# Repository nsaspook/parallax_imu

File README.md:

# vcan

pic32mkmc Viision can motor tester
# parallax_imu

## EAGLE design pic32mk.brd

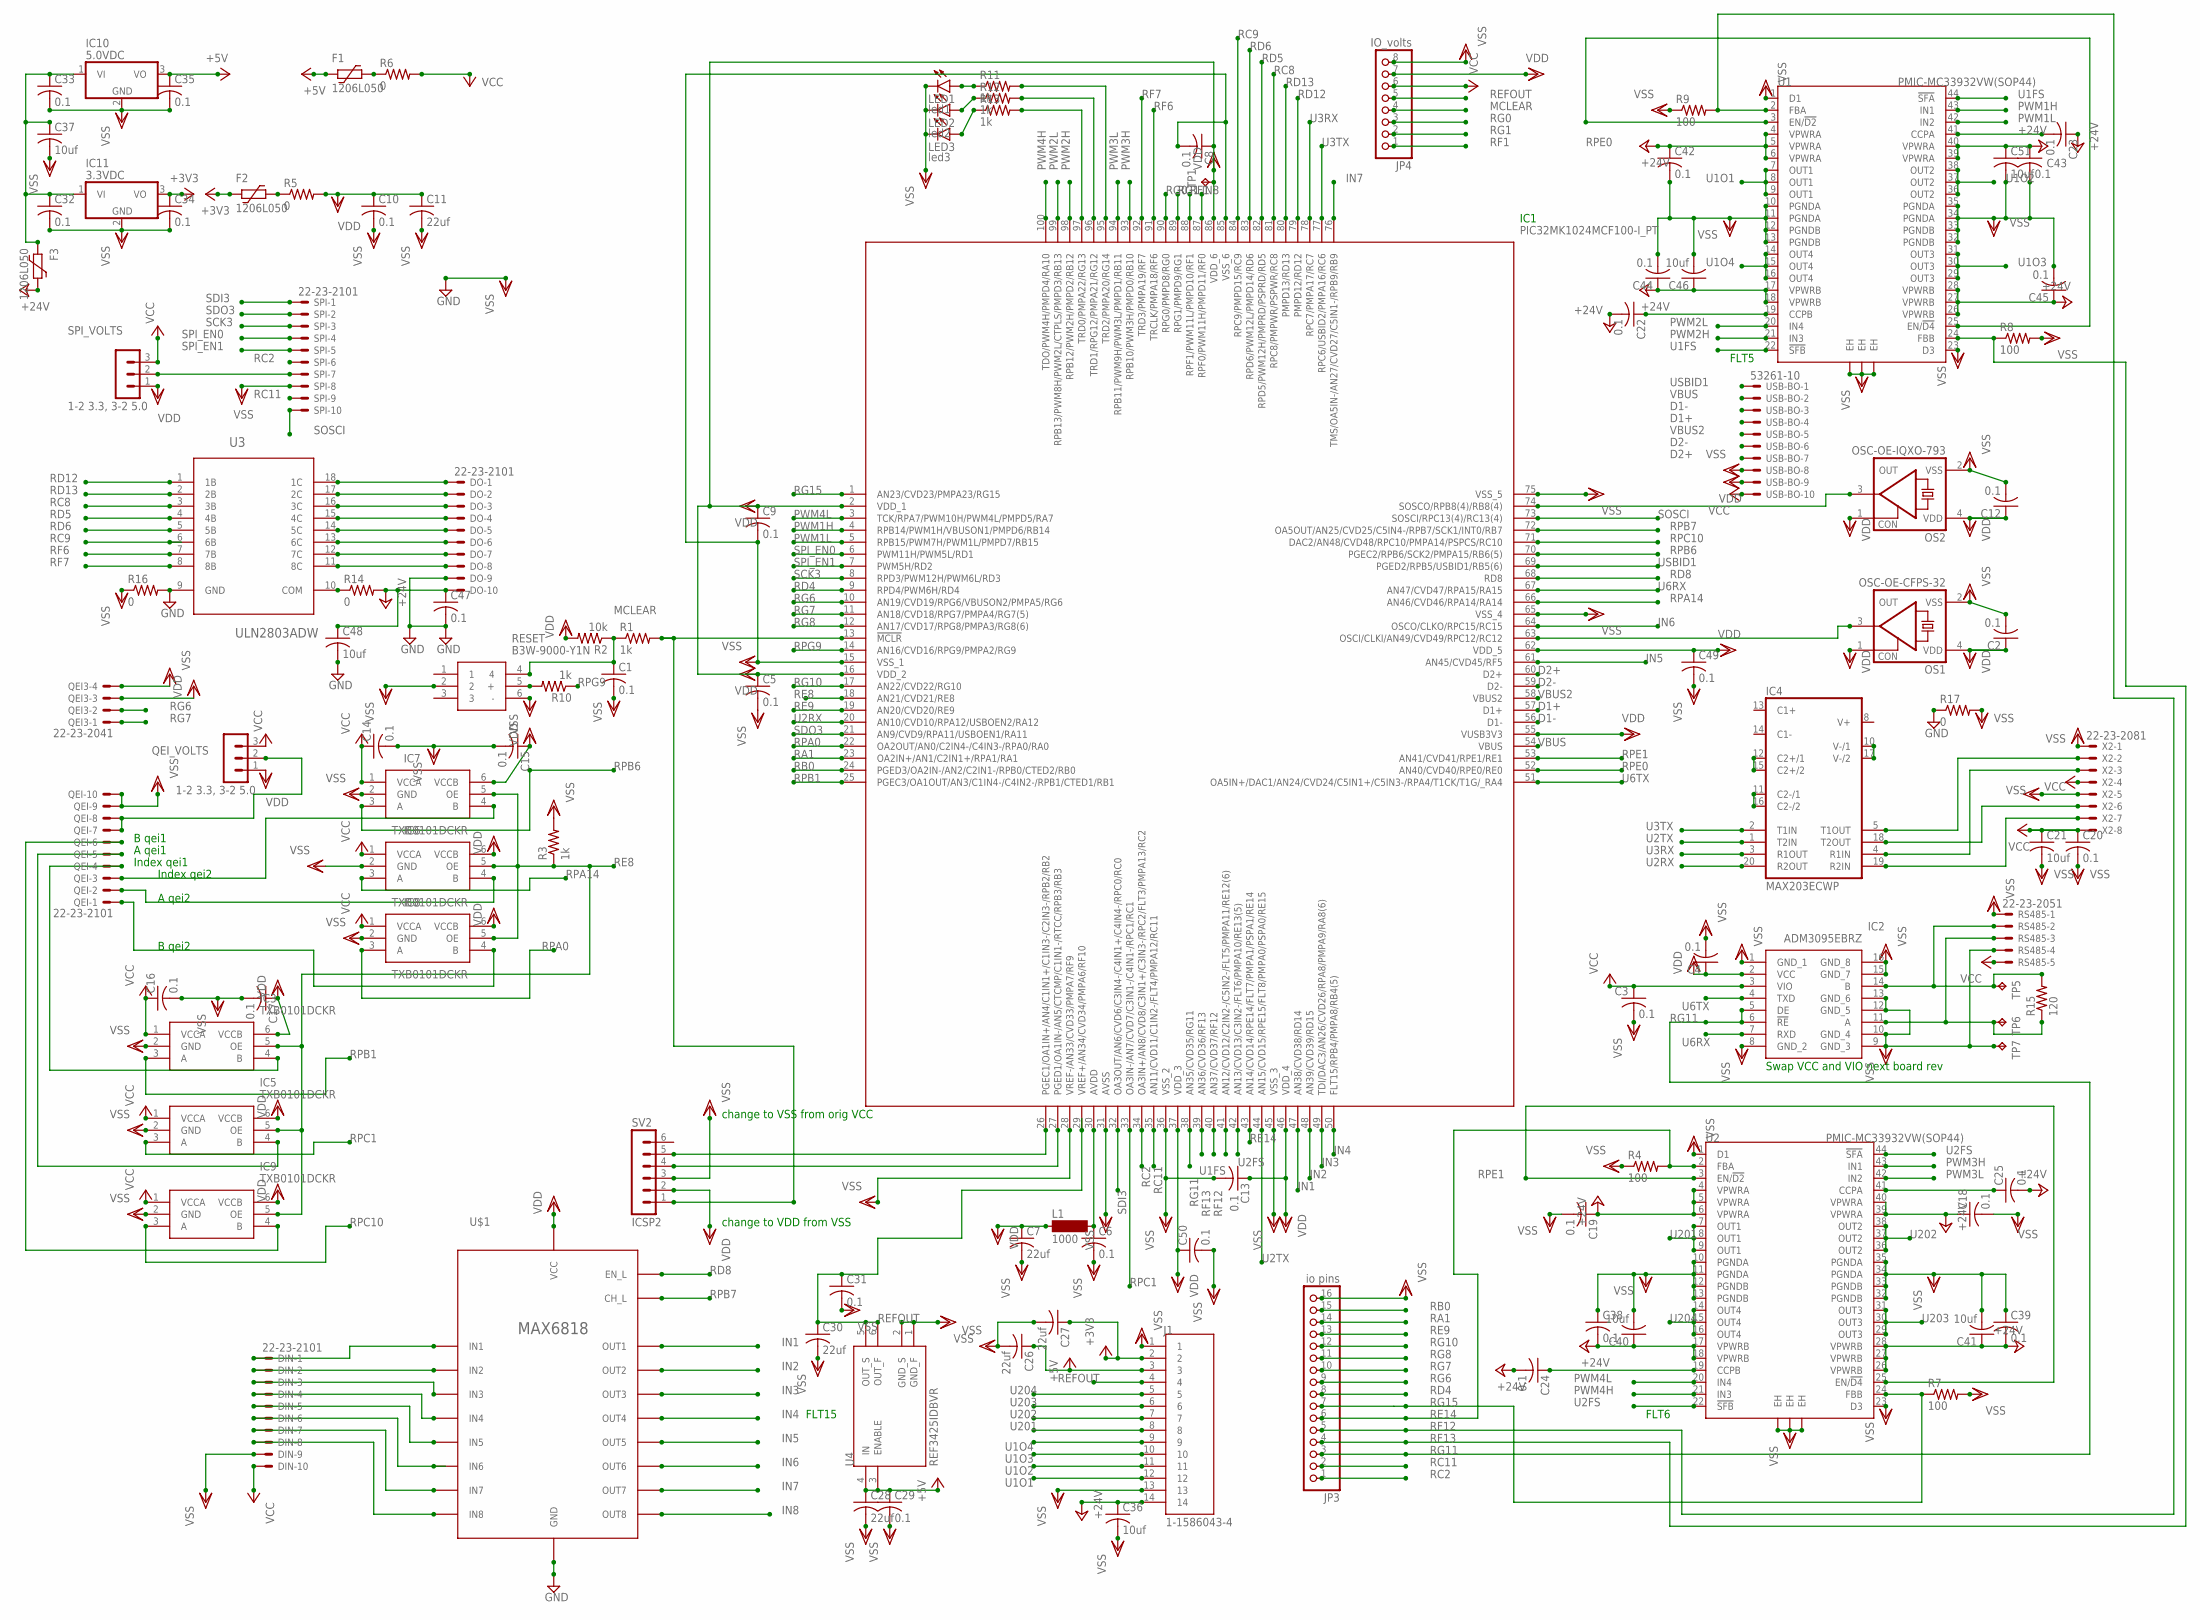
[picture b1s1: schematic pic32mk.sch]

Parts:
C1, C2, C3, C4, C5, C6, C8, C9, C10, C12, C13, C14, C15, C16, C17, C18, C19, C20, C22, C23, C24, C25, C29, C31, C32, C33, C34, C35, C38, C39, C42, C43, C44, C45, C47, C49, C50: 0.1; C0805
C7, C11, C26, C27, C28, C30: 22uf; C0805
C21, C36, C37, C40, C41, C46, C48, C51: 10uf; C1206
DIN: 22-23-2101
DO: 22-23-2101
F1, F2, F3: 1206L050; 1206L
IC1: PIC32MK1024MCF100-I_PT; QFP40P1400X1400X120-100N
IC2: ADM3095EBRZ; SOIC127P600X175-16N
IC3, IC5, IC6, IC7, IC8, IC9: TXB0101DCKR; SOT65P210X110-6N
IC4: MAX203ECWP; SO20L
IC10: 5.0VDC; TO220H
IC11: 3.3VDC; TO220H
J1: 1-1586043-4; TE_1-1586043-4
JP3: io pins; 1X16
JP4: IO_volts; 1X08
L1: 1000; SM-1206
LED1: led1; CHIPLED_1206
LED2: led2; CHIPLED_1206
LED3: led3; CHIPLED_1206
OS1: OSC-OE-CFPS-32; 7.2X5.2-4-PAD
OS2: OSC-OE-IQXO-793; 2.5X2-4-PAD
QEI: 22-23-2101
QEI3: 22-23-2041
QEI_VOLTS: 1-2 3.3, 3-2 5.0; MA03-1
R1, R3, R10, R11, R12, R13: 1k; M0805
R2: 10k; M0805
R4, R7, R8, R9: 100; R0805
R5, R6, R14, R16, R17: 0; M0805
R15: 120; R0805
RESET: B3W-9000-Y1N; B3W-9_1-LED
RS485: 22-23-2051
SPI: 22-23-2101
SPI_VOLTS: 1-2 3.3, 3-2 5.0; MA03-1
SV2: ICSP2; MA06-1
TP1, TP5, TP6, TP7: TPB1,27; B1,27
U1, U2: PMIC-MC33932VW(SOP44); SOP44-0.65-15.8X10.9MM
U3: ULN2803ADW; SOIC127P1030X265-18N
U4: REF3425IDBVR; SOT95P280X145-6N
U$1: MAX6818; SSOP20
USB-BO: 53261-10
X2: 22-23-2081

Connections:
+3V3: C27.1, C34.1, F2.2, IC11.3 (VO), J1.2
+5V: C26.1, C28.1, C29.1, C35.1, F1.2, IC10.3 (VO), J1.3, U4.3 (ENABLE), U4.4 (IN)
+24V: C18.1, C19.1, C22.2, C23.1, C24.2, C25.2, C36.1, C38.2, C39.2, C40.1, C41.1, C42.1, C43.1, C44.1, C45.1, C46.1, C47.1, C48.1, C51.1, DO.10, F3.1, J1.14, R14.2, U1.4 (VPWRA), U1.5 (VPWRA), U1.6 (VPWRA), U1.17 (VPWRB), U1.18 (VPWRB), U1.26 (VPWRB), U1.27 (VPWRB), U1.28 (VPWRB), U1.39 (VPWRA), U1.40 (VPWRA), U2.4 (VPWRA), U2.5 (VPWRA), U2.6 (VPWRA), U2.17 (VPWRB), U2.18 (VPWRB), U2.26 (VPWRB), U2.27 (VPWRB), U2.28 (VPWRB), U2.39 (VPWRA), U2.40 (VPWRA)
D1+: IC1.57 (D1+), USB-BO.4
D1-: IC1.56 (D1-), USB-BO.3
D2+: IC1.60 (D2+), USB-BO.7
D2-: IC1.59 (D2-), USB-BO.6
GND: C47.2, C48.2, DO.9, IC4.6 (GND), IC4.9 (GND), R16.2, R17.1, U3.9 (GND), U$1.GND
IN1: IC1.47 (AN38/CVD38/RD14), U$1.OUT1
IN2: IC1.48 (AN39/CVD39/RD15), U$1.OUT2
IN3: IC1.49 (TDI/DAC3/AN26/CVD26/RPA8/PMPA9/RA8(6)), U$1.OUT3
IN4: IC1.50 (FLT15/RPB4/PMPA8/RB4(5)), U$1.OUT4
IN5: IC1.61 (AN45/CVD45/RF5), U$1.OUT5
IN6: IC1.64 (OSCO/CLKO/RPC15/RC15), U$1.OUT6
IN7: IC1.76 (TMS/OA5IN-/AN27/CVD27/C5IN1-/RPB9/RB9), U$1.OUT7
IN8: IC1.87 (RPF0/PWM11H/PMPD11/RF0), U$1.OUT8
MCLEAR: C1.1, JP4.4, R1.1, R2.1, RESET.4
unnamed: IC1.74 (SOSCO/RPB8(4)/RB8(4)), OS2.3 (OUT)
unnamed: IC1.13 (!MCLR), R1.2, SV2.1
unnamed: F2.1, R5.1
unnamed: DIN.1, U$1.IN1
unnamed: IC3.4 (B), QEI.4
unnamed: C6.1, IC1.30 (AVDD), L1.2
unnamed: IC1.63 (OSCI/CLKI/AN49/CVD49/RPC12/RC12), OS1.3 (OUT)
unnamed: IC5.4 (B), QEI.5
unnamed: F1.1, R6.1
unnamed: IC8.4 (B), QEI.1
unnamed: IC6.4 (B), QEI.2
unnamed: IC7.4 (B), QEI.3
unnamed: IC1.27 (PGED1/OA1IN-/AN5/CTCMP/C1IN1-/RTCC/RPB3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), SV2.4
unnamed: IC1.26 (PGEC1/OA1IN+/AN4/C1IN1+/C1IN3-/C2IN3-/R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), SV2.5
unnamed: IC9.4 (B), QEI.6
unnamed: SPI.7, SPI_VOLTS.2
unnamed: DIN.2, U$1.IN2
unnamed: DIN.3, U$1.IN3
unnamed: DIN.4, U$1.IN4
unnamed: DIN.5, U$1.IN5
unnamed: DIN.6, U$1.IN6
unnamed: DIN.7, U$1.IN7
unnamed: DIN.8, U$1.IN8
unnamed: C22.1, U1.19 (CCPB)
unnamed: C23.2, U1.41 (CCPA)
unnamed: C24.1, U2.19 (CCPB)
unnamed: C25.1, U2.41 (CCPA)
unnamed: QEI.7, QEI.8, QEI_VOLTS.2
unnamed: C32.1, C33.1, C37.1, F3.2, IC10.1 (VI), IC11.1 (VI)
unnamed: R10.2, RESET.5 (+)
unnamed: IC1.95 (TRD2/PMPA20/RG14), R11.2
unnamed: IC1.96 (TRD1/RPG12/PMPA21/RG12), R12.2
unnamed: IC1.97 (TRD0/PMPA22/RG13), R13.2
unnamed: LED1.A, R11.1
unnamed: LED2.A, R12.1
unnamed: LED3.A, R13.1
unnamed: IC2.14 (B), R15.2, RS485.2, TP5.TP
unnamed: IC2.11 (A), R15.1, RS485.3, TP6.TP
unnamed: IC4.10 (V-/1), IC4.17 (V-/2)
unnamed: IC4.11 (C2-/1), IC4.16 (C2-/2)
unnamed: IC4.12 (C2+/1), IC4.15 (C2+/2)
unnamed: IC4.5 (T1OUT), X2.2
unnamed: IC4.4 (R1IN), X2.3
unnamed: DO.1, U3.18 (1C)
unnamed: DO.2, U3.17 (2C)
unnamed: DO.3, U3.16 (3C)
unnamed: DO.4, U3.15 (4C)
unnamed: DO.5, U3.14 (5C)
unnamed: DO.6, U3.13 (6C)
unnamed: DO.7, U3.12 (7C)
unnamed: DO.8, U3.11 (8C)
unnamed: R14.1, U3.10 (COM)
unnamed: IC4.18 (T2OUT), X2.6
unnamed: IC4.19 (R2IN), X2.7
PWM1H: IC1.4 (RPB14/PWM1H/VBUSON1/PMPD6/RB14), U1.43 (IN1)
PWM1L: IC1.5 (RPB15/PWM7H/PWM1L/PMPD7/RB15), U1.42 (IN2)
PWM2H: IC1.98 (RPB12/PWM2H/PMPD2/RB12), U1.21 (IN3)
PWM2L: IC1.99 (RPB13/PWM8H/PWM2L/CTPLS/PMPD3/RB13), U1.20 (IN4)
PWM3H: IC1.93 (RPB10/PWM3H/PMPD0/RB10), U2.43 (IN1)
PWM3L: IC1.94 (RPB11/PWM9H/PWM3L/PMPD1/RB11), U2.42 (IN2)
PWM4H: IC1.100 (TDO/PWM4H/PMPD4/RA10), U2.21 (IN3)
PWM4L: IC1.3 (TCK/RPA7/PWM10H/PWM4L/PMPD5/RA7), U2.20 (IN4)
RA1: IC1.23 (OA2IN+/AN1/C2IN1+/RPA1/RA1), JP3.14
RB0: IC1.24 (PGED3/OA2IN-/AN2/C2IN1-/RPB0/CTED2/RB0), JP3.15
RC2: IC1.34 (OA3IN+/AN8/CVD8/C3IN1+/C3IN3-/RPC2/FLT3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), JP3.1, SPI.6
RC8: IC1.81 (RPC8/PMPWR/PSPWR/RC8), U3.3 (3B)
RC9: IC1.84 (RPC9/PMPD15/RC9), U3.6 (6B)
RC11: IC1.35 (AN11/CVD11/C1IN2-/FLT4/PMPA12/RC11), JP3.2, SPI.9
RD4: IC1.9 (RPD4/PWM6H/RD4), JP3.8
RD5: IC1.82 (RPD5/PWM12H/PMPRD/PSPRD/RD5), U3.4 (4B)
RD6: IC1.83 (RPD6/PWM12L/PMPD14/RD6), U3.5 (5B)
RD8: IC1.68 (RD8), U$1.EN_L
RD12: IC1.79 (PMPD12/RD12), U3.1 (1B)
RD13: IC1.80 (PMPD13/RD13), U3.2 (2B)
RE8: IC1.18 (AN21/CVD21/RE8), IC3.5 (OE), IC5.5 (OE), IC6.5 (OE), IC7.5 (OE), IC8.5 (OE), IC9.5 (OE), R3.1
RE9: IC1.19 (AN20/CVD20/RE9), JP3.13
RE14: IC1.43 (AN14/CVD14/RPE14/FLT7/PMPA1/PSPA1/RE14), JP3.6, R4.2, U2.2 (FBA)
REFOUT: C30.1, C31.1, IC1.29 (VREF+/AN34/CVD34/PMPA6/RF10), J1.4, JP4.5, U4.5 (OUT_S), U4.6 (OUT_F)
RF1: IC1.88 (RPF1/PWM11L/PMPD10/RF1), JP4.1
RF6: IC1.91 (TRCLK/PMPA18/RF6), U3.7 (7B)
RF7: IC1.92 (TRD3/PMPA19/RF7), U3.8 (8B)
RF12: IC1.40 (AN37/CVD37/RF12), JP3.5, R9.2, U1.2 (FBA)
RF13: IC1.39 (AN36/CVD36/RF13), JP3.4, R8.1, U1.24 (FBB)
RG0: IC1.90 (RPG0/PMPD8/RG0), JP4.3
RG1: IC1.89 (RPG1/PMPD9/RG1), JP4.2
RG6: IC1.10 (AN19/CVD19/RPG6/VBUSON2/PMPA5/RG6), JP3.9, QEI3.2
RG7: IC1.11 (AN18/CVD18/RPG7/PMPA4/RG7(5)), JP3.10, QEI3.1
RG8: IC1.12 (AN17/CVD17/RPG8/PMPA3/RG8(6)), JP3.11
RG10: IC1.17 (AN22/CVD22/RG10), JP3.12
RG11: IC1.38 (AN35/CVD35/RG11), IC2.5 (DE), IC2.6 (!RE), JP3.3
RG15: IC1.1 (AN23/CVD23/PMPA23/RG15), JP3.7, R7.1, U2.24 (FBB)
RPA0: IC1.22 (OA2OUT/AN0/C2IN4-/C4IN3-/RPA0/RA0), IC8.3 (A)
RPA14: IC1.66 (AN46/CVD46/RPA14/RA14), IC6.3 (A)
RPB1: IC1.25 (PGEC3/OA1OUT/AN3/C1IN4-/C4IN2-/RPB1/CTE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), IC3.3 (A)
RPB6: IC1.70 (PGEC2/RPB6/SCK2/PMPA15/RB6(5)), IC7.3 (A)
RPB7: IC1.72 (OA5OUT/AN25/CVD25/C5IN4-/RPB7/SCK1/INT0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), U$1.CH_L
RPC1: IC1.33 (OA3IN-/AN7/CVD7/C3IN1-/C4IN1-/RPC1/RC1), IC5.3 (A)
RPC10: IC1.71 (DAC2/AN48/CVD48/RPC10/PMPA14/PSPCS/RC10), IC9.3 (A)
RPE0: IC1.52 (AN40/CVD40/RPE0/RE0), U1.3 (EN/!D2), U1.25 (EN/!D4)
RPE1: IC1.53 (AN41/CVD41/RPE1/RE1), U2.3 (EN/!D2), U2.25 (EN/!D4)
RPG9: IC1.14 (AN16/CVD16/RPG9/PMPA2/RG9), R10.1
SCK3: IC1.8 (RPD3/PWM12H/PWM6L/RD3), SPI.3
SDI3: IC1.32 (OA3OUT/AN6/CVD6/C3IN4-/C4IN1+/C4IN4-/RP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), SPI.1
SDO3: IC1.21 (AN9/CVD9/RPA11/USBOEN1/RA11), SPI.2
SOSCI: IC1.73 (SOSCI/RPC13(4)/RC13(4)), SPI.10
SPI_EN0: IC1.6 (PWM11H/PWM5L/RD1), SPI.4
SPI_EN1: IC1.7 (PWM5H/RD2), SPI.5
U1FS: IC1.41 (AN12/CVD12/C2IN2-/C5IN2-/FLT5/PMPA11/RE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), U1.22 (!SFB), U1.44 (!SFA)
U1O1: J1.12, U1.7 (OUT1), U1.8 (OUT1), U1.9 (OUT1)
U1O2: J1.11, U1.36 (OUT2), U1.37 (OUT2), U1.38 (OUT2)
U1O3: J1.10, U1.29 (OUT3), U1.30 (OUT3), U1.31 (OUT3)
U1O4: J1.9, U1.14 (OUT4), U1.15 (OUT4), U1.16 (OUT4)
U2FS: IC1.42 (AN13/CVD13/C3IN2-/FLT6/PMPA10/RE13(5)), U2.22 (!SFB), U2.44 (!SFA)
U2RX: IC1.20 (AN10/CVD10/RPA12/USBOEN2/RA12), IC4.20 (R2OUT)
U2TX: IC1.44 (AN15/CVD15/RPE15/FLT8/PMPA0/PSPA0/RE15), IC4.1 (T2IN)
U3RX: IC1.78 (RPC7/PMPA17/RC7), IC4.3 (R1OUT)
U3TX: IC1.77 (RPC6/USBID2/PMPA16/RC6), IC4.2 (T1IN)
U6RX: IC1.67 (AN47/CVD47/RPA15/RA15), IC2.7 (RXD)
U6TX: IC1.51 (OA5IN+/DAC1/AN24/CVD24/C5IN1+/C5IN3-/RP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), IC2.4 (TXD)
U201: J1.8, U2.7 (OUT1), U2.8 (OUT1), U2.9 (OUT1)
U202: J1.7, U2.36 (OUT2), U2.37 (OUT2), U2.38 (OUT2)
U203: J1.6, U2.29 (OUT3), U2.30 (OUT3), U2.31 (OUT3)
U204: J1.5, U2.14 (OUT4), U2.15 (OUT4), U2.16 (OUT4)
USBID1: IC1.69 (PGED2/RPB5/USBID1/RB5(6)), USB-BO.1
VBUS: IC1.54 (VBUS), USB-BO.2
VBUS2: IC1.58 (VBUS2), USB-BO.5
VCC: C3.1, C14.1, C16.1, C20.1, C21.1, DIN.10, IC2.3 (VIO), IC3.1 (VCCA), IC4.7 (VCC), IC5.1 (VCCA), IC6.1 (VCCA), IC7.1 (VCCA), IC8.1 (VCCA), IC9.1 (VCCA), JP4.6, QEI_VOLTS.3, R6.2, RS485.5, SPI_VOLTS.3, USB-BO.10, X2.4, X2.8
VDD: C2.1, C4.1, C5.1, C7.1, C8.1, C9.1, C10.1, C11.1, C12.1, C13.1, C15.1, C17.1, C49.1, C50.1, IC1.2 (VDD_1), IC1.16 (VDD_2), IC1.37 (VDD_3), IC1.46 (VDD_4), IC1.55 (VUSB3V3), IC1.62 (VDD_5), IC1.86 (VDD_6), IC2.2 (VCC), IC3.6 (VCCB), IC5.6 (VCCB), IC6.6 (VCCB), IC7.6 (VCCB), IC8.6 (VCCB), IC9.6 (VCCB), JP4.7, L1.1, OS1.1 (CON), OS1.4 (VDD), OS2.1 (CON), OS2.4 (VDD), QEI3.3, QEI_VOLTS.1, R2.2, R5.2, SPI_VOLTS.1, SV2.2, TP1.TP, U$1.VCC, USB-BO.9
VSS: C1.2, C2.2, C3.2, C4.2, C5.2, C6.2, C7.2, C8.2, C9.2, C10.2, C11.2, C12.2, C13.2, C14.2, C15.2, C16.2, C17.2, C18.2, C19.2, C20.2, C21.2, C26.2, C27.2, C28.2, C29.2, C30.2, C31.2, C32.2, C33.2, C34.2, C35.2, C36.2, C37.2, C38.1, C39.1, C40.2, C41.2, C42.2, C43.2, C44.2, C45.2, C46.2, C49.2, C50.2, C51.2, DIN.9, IC1.15 (VSS_1), IC1.28 (VREF-/AN33/CVD33/PMPA7/RF9), IC1.31 (AVSS), IC1.36 (VSS_2), IC1.45 (VSS_3), IC1.65 (VSS_4), IC1.75 (VSS_5), IC1.85 (VSS_6), IC2.1 (GND_1), IC2.8 (GND_2), IC2.9 (GND_3), IC2.10 (GND_4), IC2.12 (GND_5), IC2.13 (GND_6), IC2.15 (GND_7), IC2.16 (GND_8), IC3.2 (GND), IC5.2 (GND), IC6.2 (GND), IC7.2 (GND), IC8.2 (GND), IC9.2 (GND), IC10.2 (GND), IC11.2 (GND), J1.1, J1.13, JP3.16, JP4.8, LED1.C, LED2.C, LED3.C, OS1.2 (VSS), OS2.2 (VSS), QEI.9, QEI.10, QEI3.4, R3.2, R4.1, R7.2, R8.2, R9.1, R16.1, R17.2, RESET.2, RESET.6 (-), RS485.1, RS485.4, SPI.8, SV2.3, TP7.TP, U1.1 (D1), U1.10 (PGNDA), U1.11 (PGNDA), U1.12 (PGNDB), U1.13 (PGNDB), U1.23 (D3), U1.32 (PGNDB), U1.33 (PGNDB), U1.34 (PGNDA), U1.35 (PGNDA), U1.EH@1 (EH), U1.EH@2 (EH), U1.EH@3 (EH), U2.1 (D1), U2.10 (PGNDA), U2.11 (PGNDA), U2.12 (PGNDB), U2.13 (PGNDB), U2.23 (D3), U2.32 (PGNDB), U2.33 (PGNDB), U2.34 (PGNDA), U2.35 (PGNDA), U2.EH@1 (EH), U2.EH@2 (EH), U2.EH@3 (EH), U4.1 (GND_F), U4.2 (GND_S), USB-BO.8, X2.1, X2.5

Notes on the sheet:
change to VDD from VSS
change to VSS from orig VCC
A qei2
B qei2
Index qei2
Index qei1
A qei1
B qei1
FLT6
FLT5
FLT15
Swap VCC and VIO next board rev

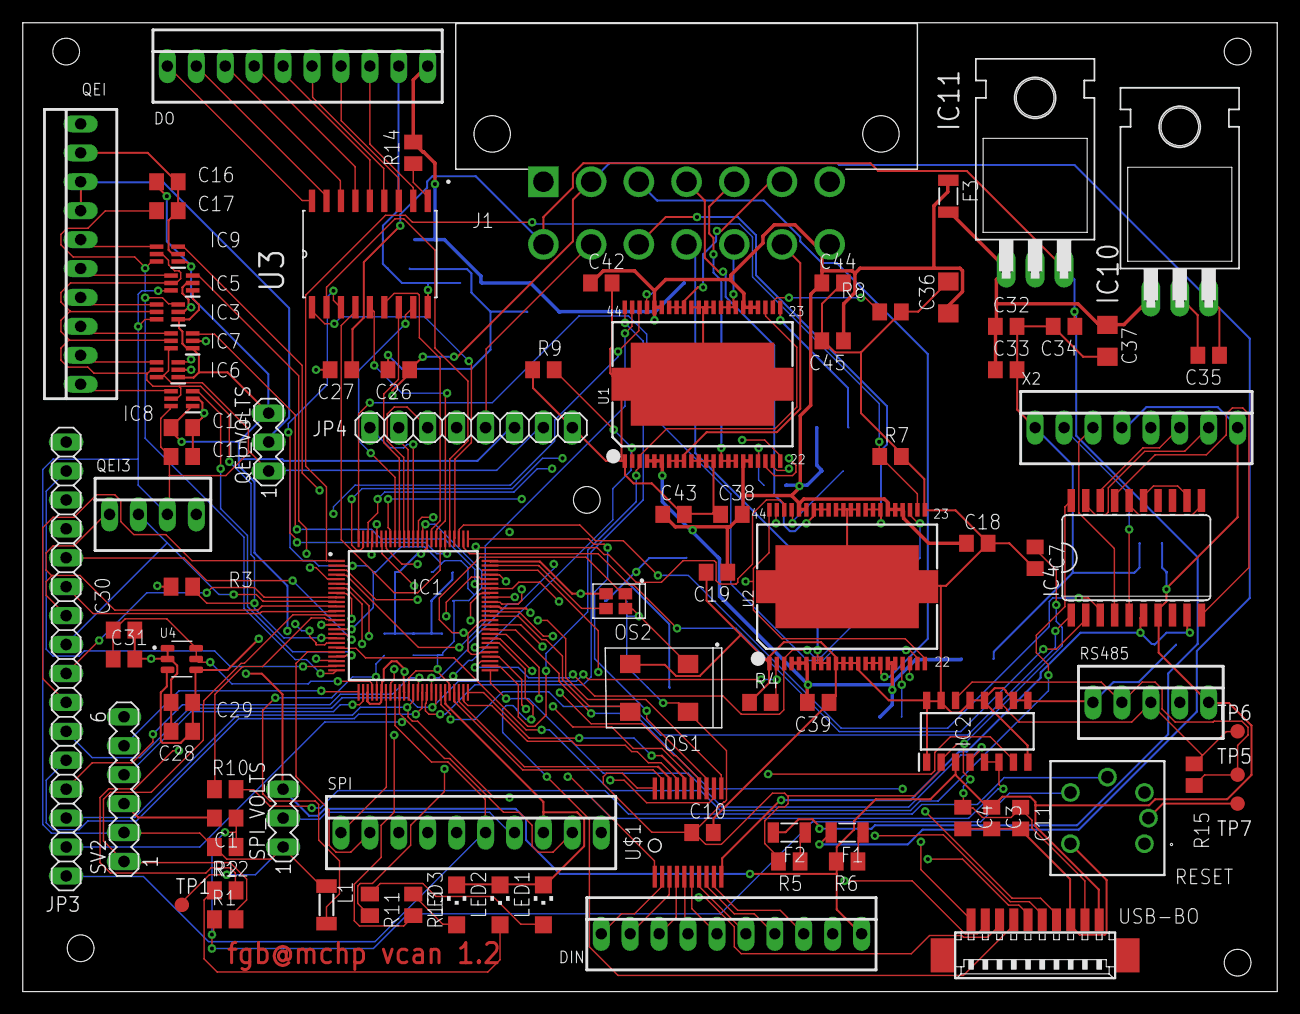
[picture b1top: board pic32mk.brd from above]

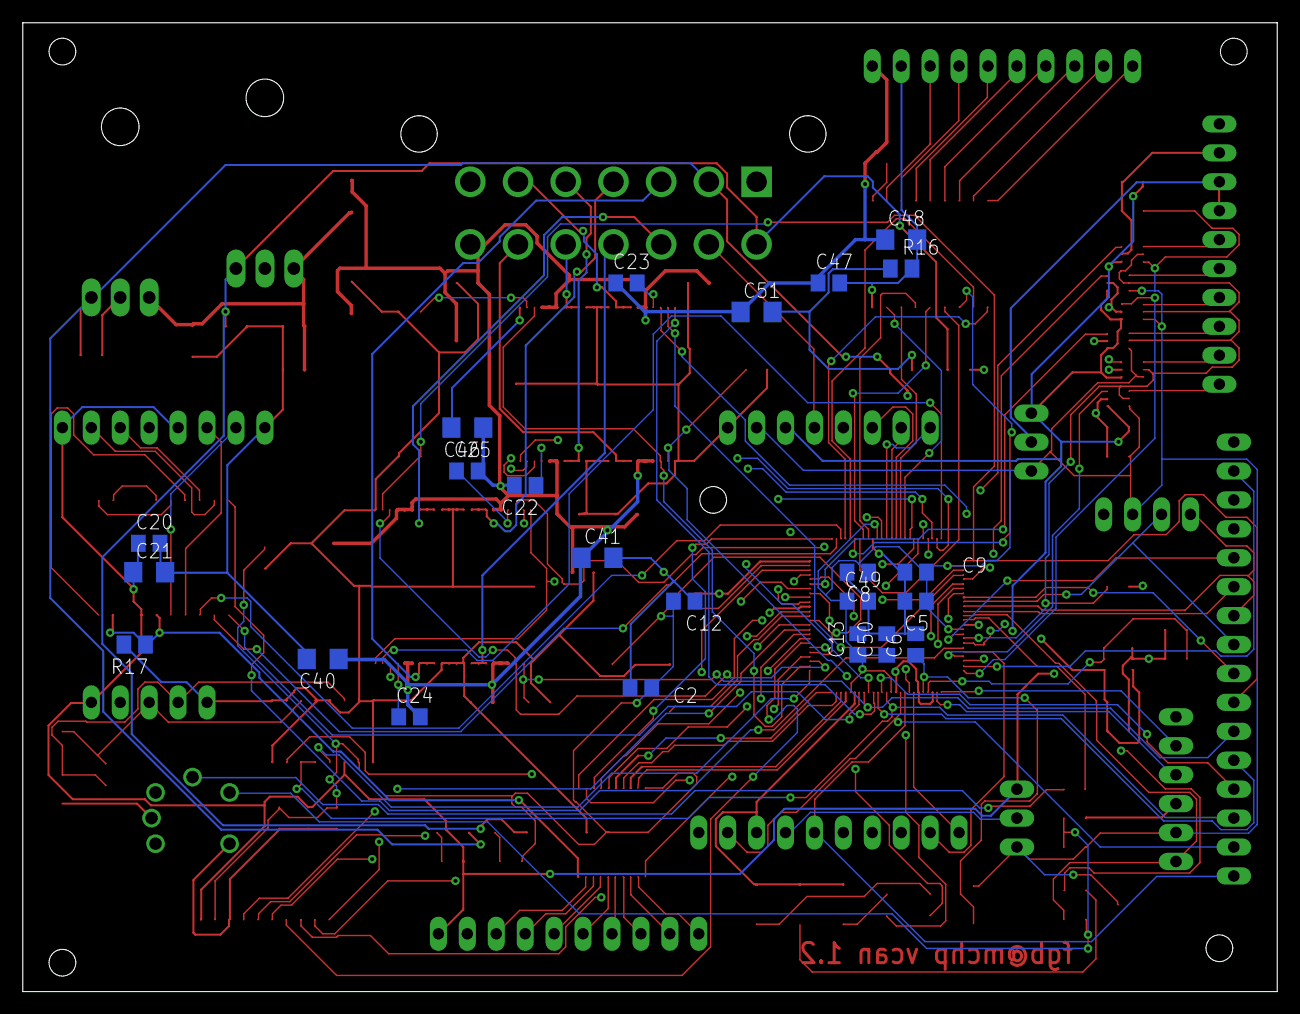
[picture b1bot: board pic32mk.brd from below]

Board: 4 copper layers, 110.2 x 85.1 mm, 112 parts (23 on the bottom side), 146 nets.

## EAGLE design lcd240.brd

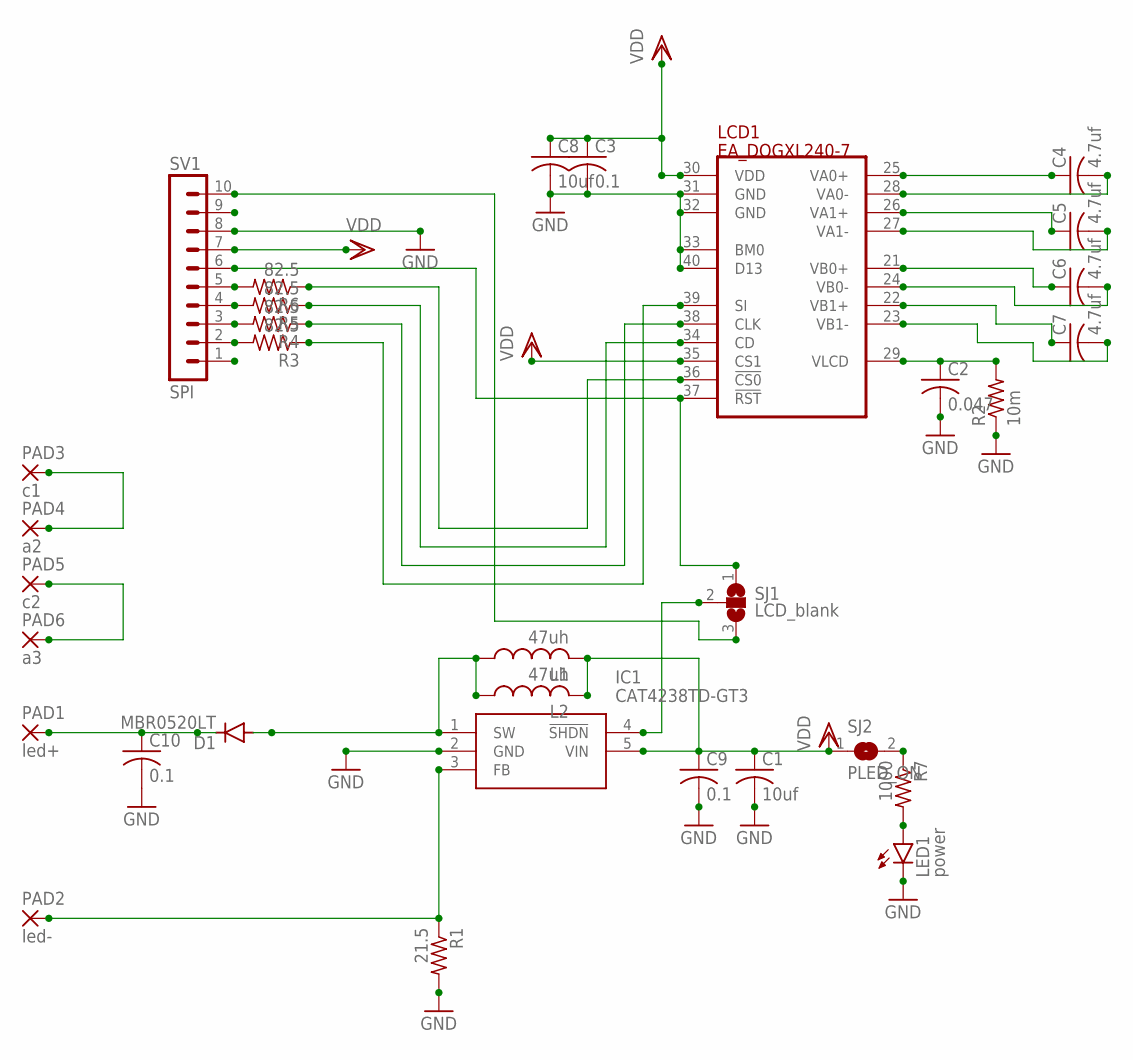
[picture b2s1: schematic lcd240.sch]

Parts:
C1, C8: 10uf; C1206
C2: 0.047; C1206
C3, C9, C10: 0.1; C1206
C4, C5, C6, C7: 4.7uf; C1206
D1: MBR0520LT; SOD123
IC1: CAT4238TD-GT3; SOT95P280X100-5N
L1: 47uh; 0204/5
L2: 47uh; L2012C
LCD1: EA_DOGXL240-7
LED1: power; SML0805
PAD1: led+; 1,6/0,8
PAD2: led-; 1,6/0,8
PAD3: c1; 1,6/0,8
PAD4: a2; 1,6/0,8
PAD5: c2; 1,6/0,8
PAD6: a3; 1,6/0,8
R1: 21.5; R0805
R2: 10m; R0805
R3, R4, R5, R6: 82.5; R0805
R7: 1000; R0805
SJ1: LCD_blank; SJ_2
SJ2: PLED_ON; SJ
SV1: SPI; MA10-1

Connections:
GND: C1.2, C2.2, C3.2, C8.2, C9.2, C10.2, IC1.2 (GND), LCD1.31 (GND), LCD1.32 (GND), LCD1.33 (BM0), LCD1.40 (D13), LED1.C, R1.2, R2.1, SV1.8
unnamed: C4.2, LCD1.28 (VA0-)
unnamed: C5.1, LCD1.26 (VA1+)
unnamed: C2.1, LCD1.29 (VLCD), R2.2
unnamed: LCD1.37 (!RST!), SJ1.1, SV1.6
unnamed: C5.2, LCD1.27 (VA1-)
unnamed: C4.1, LCD1.25 (VA0+)
unnamed: C6.1, LCD1.21 (VB0+)
unnamed: C6.2, LCD1.24 (VB0-)
unnamed: C7.1, LCD1.22 (VB1+)
unnamed: C7.2, LCD1.23 (VB1-)
unnamed: LCD1.36 (!CS0!), R6.1
unnamed: LCD1.34 (CD), R5.1
unnamed: LCD1.38 (CLK), R4.1
unnamed: LCD1.39 (SI), R3.1
unnamed: C10.1, D1.C, PAD1.1
unnamed: SJ1.3, SV1.10
unnamed: R3.2, SV1.2
unnamed: R4.2, SV1.3
unnamed: R6.2, SV1.5
unnamed: R5.2, SV1.4
unnamed: D1.A, IC1.1 (SW), L1.1, L2.1
unnamed: IC1.3 (FB), PAD2.1, R1.1
unnamed: PAD3.1, PAD4.1
unnamed: PAD5.1, PAD6.1
unnamed: IC1.4 (!SHDN), SJ1.2
unnamed: R7.1, SJ2.2
unnamed: LED1.A, R7.2
VDD: C1.1, C3.1, C8.1, C9.1, IC1.5 (VIN), L1.2, L2.2, LCD1.30 (VDD), LCD1.35 (CS1), SJ2.1, SV1.7

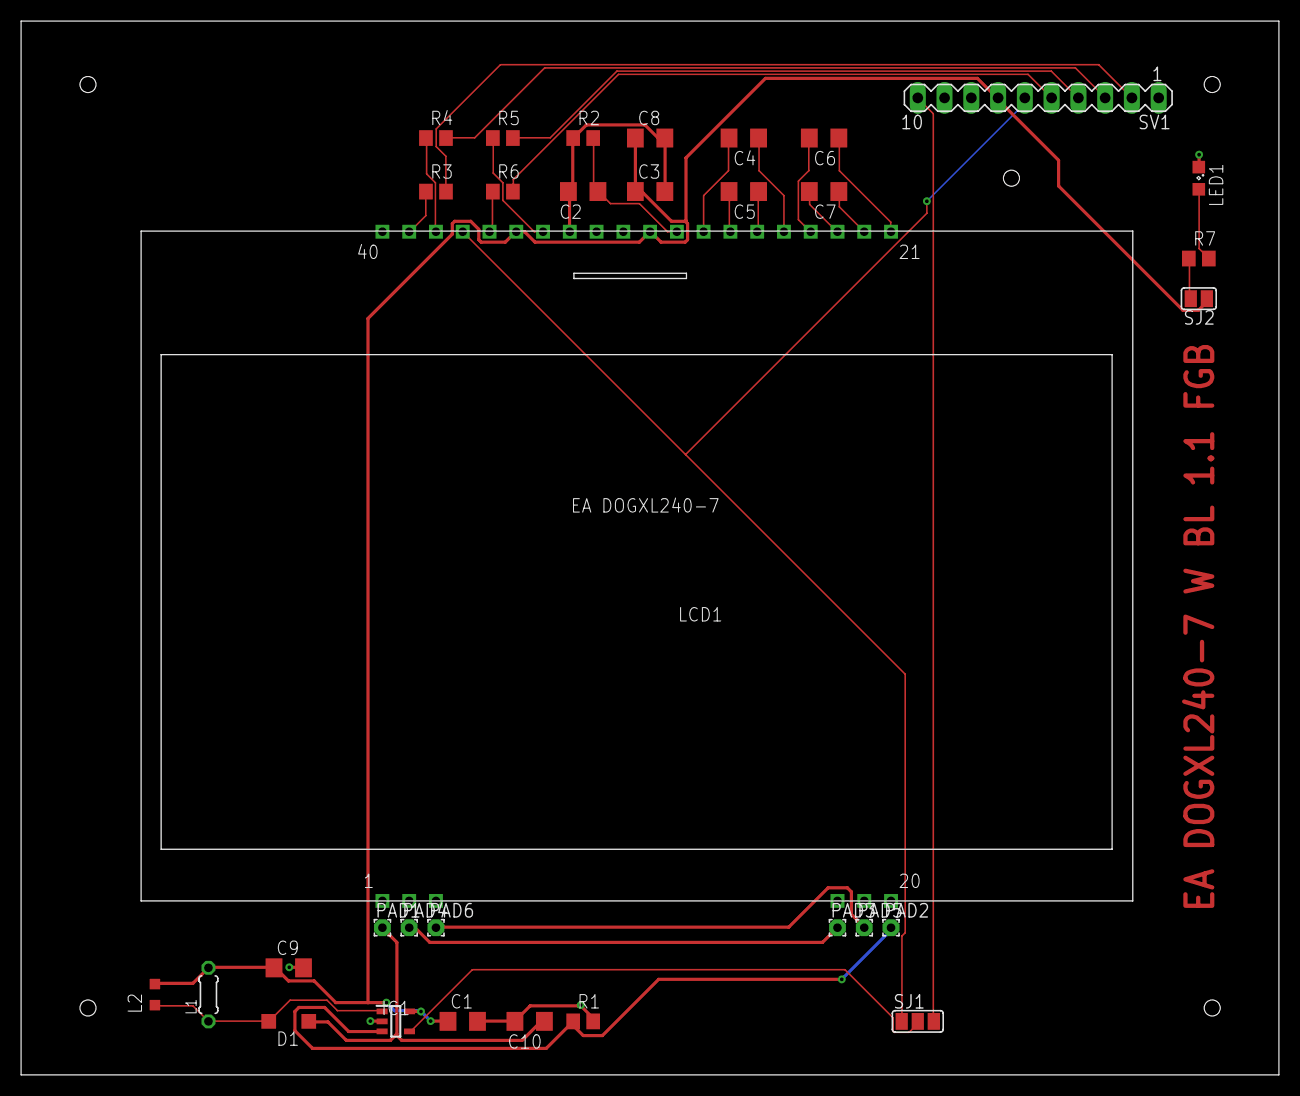
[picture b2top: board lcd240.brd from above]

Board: 2 copper layers, 119.4 x 100.0 mm, 32 parts (0 on the bottom side), 29 nets.

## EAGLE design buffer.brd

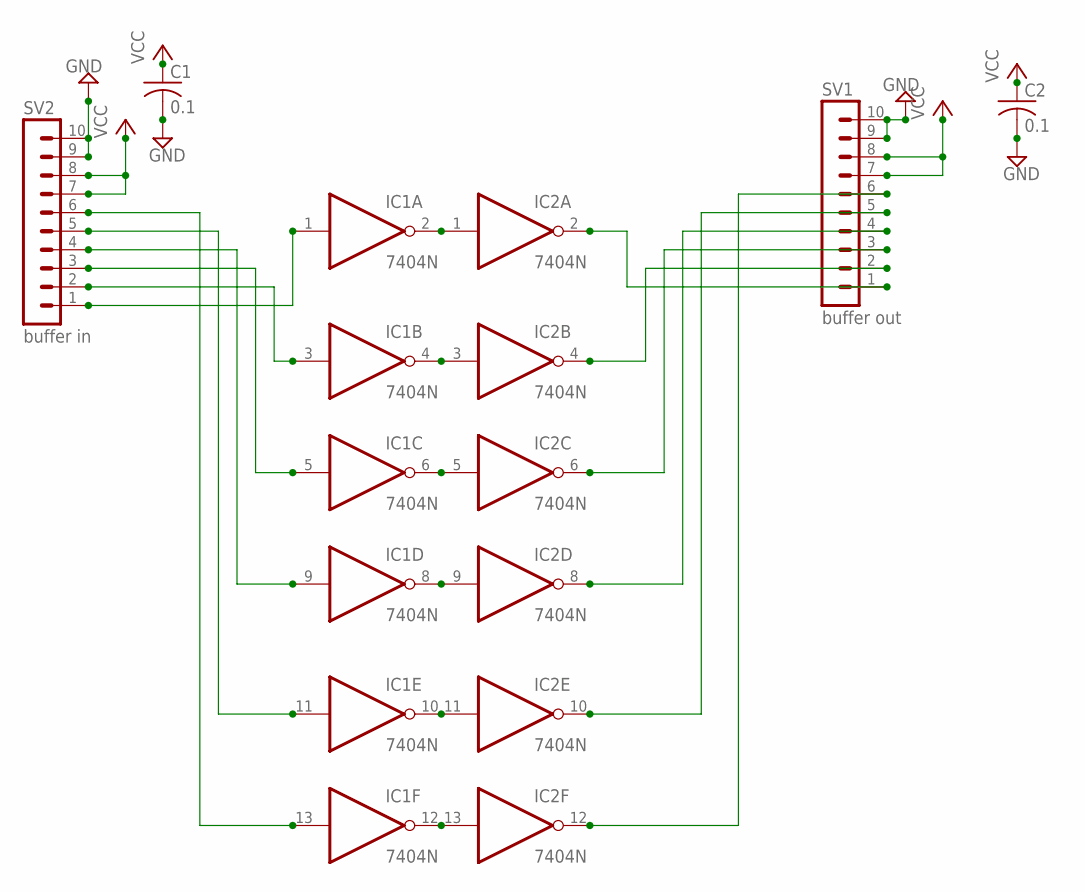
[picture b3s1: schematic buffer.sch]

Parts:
C1, C2: 0.1; C1206
IC1, IC2: 7404N; DIL14
SV1: buffer out; MA10-1
SV2: buffer in; MA10-1

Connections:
GND: C1.2, C2.2, IC1.7 (GND), IC2.7 (GND), SV1.9, SV1.10, SV2.9, SV2.10
unnamed: IC1.4 (O), IC2.3 (I)
unnamed: IC1.6 (O), IC2.5 (I)
unnamed: IC1.8 (O), IC2.9 (I)
unnamed: IC1.10 (O), IC2.11 (I)
unnamed: IC1.12 (O), IC2.13 (I)
unnamed: IC1.2 (O), IC2.1 (I)
unnamed: IC1.1 (I), SV2.1
unnamed: IC1.3 (I), SV2.2
unnamed: IC1.5 (I), SV2.3
unnamed: IC1.9 (I), SV2.4
unnamed: IC1.11 (I), SV2.5
unnamed: IC1.13 (I), SV2.6
unnamed: IC2.2 (O), SV1.1
unnamed: IC2.4 (O), SV1.2
unnamed: IC2.6 (O), SV1.3
unnamed: IC2.8 (O), SV1.4
unnamed: IC2.10 (O), SV1.5
unnamed: IC2.12 (O), SV1.6
VCC: C1.1, C2.1, IC1.14 (VCC), IC2.14 (VCC), SV1.7, SV1.8, SV2.7, SV2.8

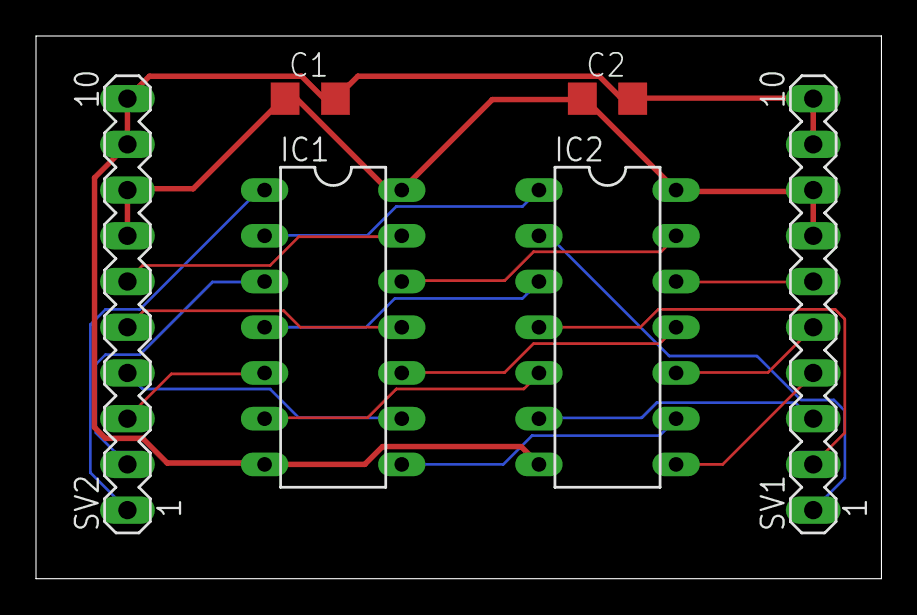
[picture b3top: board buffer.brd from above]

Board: 2 copper layers, 47.0 x 30.1 mm, 6 parts (0 on the bottom side), 20 nets.

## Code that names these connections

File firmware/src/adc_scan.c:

#include "vcan.h"
#include "adc_scan.h"

void end_of_adc_scan(void)
{
	/*
	 * check for ADC scanning done, a 'end of scan' interrupt ISR
	 */

//	DEBUGB0_Clear();
//	DEBUGB0_Set();
	if ((ADCCON2 & _ADCCON2_EOSRDY_MASK)) { //  End of Scan Interrupt Status bit
		/*
		 * update program variables from the ADC result registers
		 */
		u2ai = ADCHS_ChannelResultGet(ADCHS_CH14); // JP5 pin 6, AN14, FBA2/RE14
		u2bi = ADCHS_ChannelResultGet(ADCHS_CH23); // JP5 pin 7, AN23, FBB2/RG15
		u1ai = ADCHS_ChannelResultGet(ADCHS_CH37); // JP5 pin 5, AN37, FBA1/RF12
		u1bi = ADCHS_ChannelResultGet(ADCHS_CH36); // JP5 pin 4, AN36, FBB1/RF13
//		an_data[ANA1] = ADCHS_ChannelResultGet(ADCHS_CH1); // JP5 pin 14, AN1, ANA1/RA1
//		an_data[ANA3] = ADCHS_ChannelResultGet(ADCHS_CH3); // QEI pin 4, AN3, ANA3/RA3
		an_data[POT1] = ADCHS_ChannelResultGet(ADCHS_CH11); // JP5 pin 2, AN11 POT1/RC11
		an_data[POT2] = ADCHS_ChannelResultGet(ADCHS_CH17); // JP5 pin 11, AN17 POT2/RG8
		an_data[IVREF] = ADCHS_ChannelResultGet(ADCHS_CH50); // IVREF 1.2V (internal AN50), extern vref+ 2.5-V REF3425
		an_data[TSENSOR] = ADCHS_ChannelResultGet(ADCHS_CH53); //  CTMU Temperature Sensor (internal AN53)
		if (!option1_Get()) {

		}
		u1ai = (int32_t) lp_filter_f((double) u1ai, 0); // try filter
		u1bi = (int32_t) lp_filter_f((double) u1bi, 1);
		u2ai = (int32_t) lp_filter_f((double) u2ai, 2);
		u2bi = (int32_t) lp_filter_f((double) u2bi, 3);
		u_total = u1bi + u2ai + u2bi;
	}
	IFS3CLR = _IFS3_AD1EOSIF_MASK; // Clear the interrupt
#ifndef BDCM
#ifndef G400HZ
	ADCCON3SET = _ADCCON3_GSWTRG_MASK; // scan re-trigger
#endif
#endif
//	DEBUGB0_Clear();
}

void init_end_of_adc_scan(void)
{
	filters_init();

	/*
	 * AN14/pin 6, AN23/pin 7, AN36/pin 4, AN37/pin 5, AN11/pin 2, AN17/pin 11
	 * set ADC trigger to SCAN and start SCAN trigger
	 */

	ADCCON1bits.STRGSRC = 1; // set trigger source 5-bit value
	ADCCON3SET = _ADCCON3_GSWTRG_MASK; // use scan trigger

	IFS3CLR = _IFS3_AD1EOSIF_MASK; // Clear the interrupt
	IEC3SET = _IEC3_AD1EOSIE_MASK; // Enable the interrupt VECTOR

	ADCCON2SET = _ADCCON2_EOSIEN_MASK; // ENABLE EOS INTERRUPTS
}

/*
 * take ADC shunt measurement of phase current, convert to milliamps of current with possible motor current correction
 */
int32_t hb_current(const int32_t adc_value, const bool motor)
{
	double adc_step = MV_STEP;

	if (motor) {
		return(int32_t) ((((double) adc_value * adc_step) * HB_SCALE) * MOTOR_CURRENT_SCALE);
	} else {
		return(int32_t) ((((double) adc_value * adc_step) * HB_SCALE));
	}
}

void start_adc_scan(void)
{
//	DEBUGB0_Set();
	ADCCON3SET = _ADCCON3_GSWTRG_MASK; // scan re-trigger	
}

/*
 * make sure ADC conversions have good values
 */
bool check_adc_ivref(void)
{
	if ((an_data[IVREF] > ADC_L) && (an_data[IVREF] < ADC_H)) {
		return true;
	} else {
		return false;
	}
}
